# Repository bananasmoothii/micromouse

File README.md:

# [Bananasmoothii's Micromouse](https://github.com/bananasmoothii/micromouse)

A school project aiming to make a Micromouse robot and make it solve a maze (with official-size cells: 18x18 cm).

## Flash and run code

Install [Rust](https://doc.rust-lang.org/cargo/getting-started/installation.html) and [probe-rs](https://probe.rs/)
with one of the methods in their docs. Then plug the STM32F446RE Nucleo board via USB and flash and run with:

```sh
cargo run
```

(configured in `./.cargo`)

The robot has a power mechanism that cuts power when battery isn't charged enough, but this requires you to
maintain the button (on the back custom PCB) pressed when flashing the MCU. I recommend having an IDE keyboard
shortcut for this command. Flashing often fails on the first try, if it does just try again.

## Hardware used

* Nucleo board (with ST-Link): MCU is STM32F446RE
* Monster Moto shield
*
Two [IGARASHI N 2738-45 motors](https://www.conrad.fr/fr/p/moteur-universel-a-balais-brushed-igarashi-2738-048-gfc-3-244503.html)
*
One [LiPo 2S battery](https://www.conrad.fr/fr/p/reely-pack-de-batterie-lipo-7-4-v-350-mah-nombre-de-cellules-2-25-c-softcase-bec-2617149.html)
(6V - 8.4V) (bought two for using one while the other charges)
* Two 3144 Hall sensors (magnet → `DOUT = HIGH`) for odometry (12 magnets per wheel)
* One MPU 9250 (accelerometer + gyroscope + magnetometer + temperature sensor)
* Three VL53L1X distance sensors
* Tires are made from [20x7mm elastics](https://www.amazon.fr/dp/B0D9K3PJJF)
* [Cylindrical magnets, 2mm wide](https://www.amazon.fr/dp/B08NDRXGQX)

## [CAD models](https://cad.onshape.com/documents/aaf7a6983651c7702bceaa13/w/41b76918edb6f00955c96fe0/e/62dd90809362918a445464ef?renderMode=0&uiState=6a1494e0c7839ab38c881d4a)

This repo contains almost everything related to this project except the CAD models in the Onshape link above.

* The chassis is laser-cut from 3mm-thick wood and assembled with wood glue for the most stressed parts
* The wheels are made of laser-cut acrylic (wood not being resistant enough for gearing) pieces superglued together

  Note: In Onshape, the wheels are solid, you need the **Kiri:Moto** plugin to slice in 5mm slices and export as SVG for
  the laser cutter.
* The shafts are shoulder screws (unthreaded shoulder acting as the axle) screwed directly into the wooden chassis
* The smallest gear that's directly on the motors' shaft are metal, bought them
  [here](https://www.conrad.fr/fr/p/acier-roue-a-denture-frontale-reely-type-de-module-0-5-o-de-percage-2-3-mm-nombre-de-dents-12-240354.html)
* Kerf compensation was set to **0.16mm** for me (set in Kiri:Moto)

## Build & assembly manual

A full step-by-step guide to cutting the chassis, assembling the mechanics, and mounting all
electronics is available in
[issues_and_knowledge/build_manual.md](issues_and_knowledge/build_manual.md).

## Issues encountered and solutions found

A summary of the main problems hit during development — I²C crashes, missed encoder ticks,
Embassy async pitfalls, the trajectory-point-list dead end, and more — along with the solutions,
is documented in
[issues_and_knowledge/issues_list.md](issues_and_knowledge/issues_list.md).

### Robot overview

## Custom PCB

Files for the custom pcb are in the `pcb` folder and can be opened with [KiCad](https://www.kicad.org/).

### Export for manufacturing with JLCPCB

I used JLCPCB to manufacture and assemble the PCB. For generating the production files, install this KiCad plugin:

> **Fabrication Toolkit**
>
> Toolkit for automating PCB fabrication process with KiCad and JLC PCB.
>
> Features:
> - Generates gerber files in correct format for production.
> - Generates BOM file in correct format for production.
> - Generates Pick and Place file in correct format for assembly.
> - Automatic and manual component translations.
> - Many more unique additional features.

Production files will be generated in `pcb/production`. The files you're gonna need for JLCPCB are:

- `pcb.zip` (contains the Gerber files)

And for PCB assembly (PCBA):

- `bom.csv` (Bill Of Materials)
- `positions.csv` as "CPL" (Component Placement List)

## How to debug

Debugging on microcontroller can be quite tricky. For example, on the STM32F446RE, you can have **up to 6 breakpoints**
enabled, and debugging works through probe-rs. If the probe-rs' GDB stub doesn't work (probably because
[this issue](https://github.com/probe-rs/probe-rs/issues/3805) hasn't been fixed yet), try debugging through DAP.

### On VSCode

Probe-rs has made it easy to debug with VSCode thanks to an extension as explained
[here](https://probe.rs/docs/tools/debugger/)

### On RustRover

There is also an extension that can debug through DAP but it is less straight-forward:

1. Install the "lsp4ij" extension.
2. Set it up
   using [this tutorial](https://github.com/redhat-developer/lsp4ij/blob/main/docs/dap/user-defined-dap/codelldb.md).
    * At the end, you should use "attach" instead of "launch" with these parameters:

```json
{
  "chip": "STM32F446RE",
  "coreConfigs": [
    {
      "programBinary": "${file}"
    }
  ]
}
```

Note: RTT does not work here (I tried with `rttEnabled`).

## Repository structure

**For more information, see [architecture.md](issues_and_knowledge/architecture.md)**

```
micromouse/
├── src/
│   ├── main.rs                   — Embassy entry point: heap init, peripheral setup, task spawning
│   ├── dimensions.rs             — Physical constants (cell size, wall thickness, wheel geometry)
│   ├── i2c_devices.rs            — Sequential XSHUT-based I2C init for the 3 ToF sensors
│   ├── flash_log.rs              — For storing logs in flash memory
│   ├── labyrinth.rs              — 16×16 maze grid, probabilistic wall detection, pathfinding (flood-fill)
│   ├── utils.rs                  — Shared utilities
│   ├── panic_handler.rs          — Custom panic handler (logs then halts)
│   │
│   ├── devices/                  — Hardware drivers
│   │   ├── motors.rs             — DC motor PI feedback loop, reads waypoints from PATH_CHANNEL
│   │   ├── hall_sensor_3144.rs   — Interrupt-driven wheel encoders (AtomicI32 tick counters)
│   │   ├── mpu9250.rs            — 9-DOF IMU over SPI (accel, gyro, magnetometer)
│   │   ├── battery.rs            — 2-cell LiPo voltage monitoring via ADC
│   │   ├── buzzer.rs             — PWM audio (TIM2), command channel-driven
│   │   └── vl53lxx/              — ToF distance sensors
│   │       ├── vl53l0x.rs        — VL53L0X driver (unused, kept for reference)
│   │       └── vl53l1x.rs        — VL53L1X driver (distance sensors, runtime I2C address change)
│   │
│   ├── positioning/              — Sensor fusion and position tracking
│   │   ├── mod.rs                — positioning_task: 20 ms sensor-fusion loop
│   │   ├── odometry.rs           — Skid-steering wheel kinematics
│   │   ├── mpu.rs                — Gyro → yaw, magnetometer → absolute heading
│   │   ├── fusion.rs             — Kalman Filter (odometry + gyro + magnetometer)
│   │   └── types.rs              — Position2D, MovementDelta
│   │
│   └── trajectory/               — Path planning and motion profiling
│       ├── mod.rs                — Converts cell path → smooth velocity-profiled segments
│       ├── straight_line.rs      — Straight segment with trapezoidal velocity profile
│       └── in_place_turn.rs      — In-place rotation segment
│
├── docs/                         — Hosted on https://bananasmoothii.github.io/micromouse/
│   └── timeline/                 — Project timeline web app (photos, videos, notes)
│
├── pcb/                          — KiCad files for the custom PCB
│   └── production/               — JLCPCB production and assembly files
│
├── issues_and_knowledge/         — Notes on hardware quirks, bugs, and build documentation
│   ├── architecture.md           — High-level architecture overview
│   ├── build_manual.md           — Step-by-step build & assembly manual (translated from Rapport.docx)
│   ├── build_manual/             — Images referenced by build_manual.md
│   ├── issues_list.md            — Issues encountered and solutions found (translated from Rapport.docx)
│   ├── embassy_exti_missed_ticks_fix.md
│   ├── i2c_registers_and_pullups_explained.md
│   ├── monster moto shield ressources.md
│   └── vl53l1x_i2c_bsy_lockup_recovery.md
│
├── tools/                        — Various python scripts for analyzing logs with graphs or other things
│   └── clean_svg.py              — Replaces polyline-approximated circles in Kiri:Moto SVG exports with true SVG circles (fixes laser cutter charring)
│
├── build.rs                      — Build script (linker script selection)
├── Cargo.toml                    — Dependencies and patch section for forked sensor crates
├── memory.x                      — Linker memory map for STM32F446RE
└── .cargo/config.toml            — Default target (thumbv7em-none-eabi), runner (probe-rs), log level
```

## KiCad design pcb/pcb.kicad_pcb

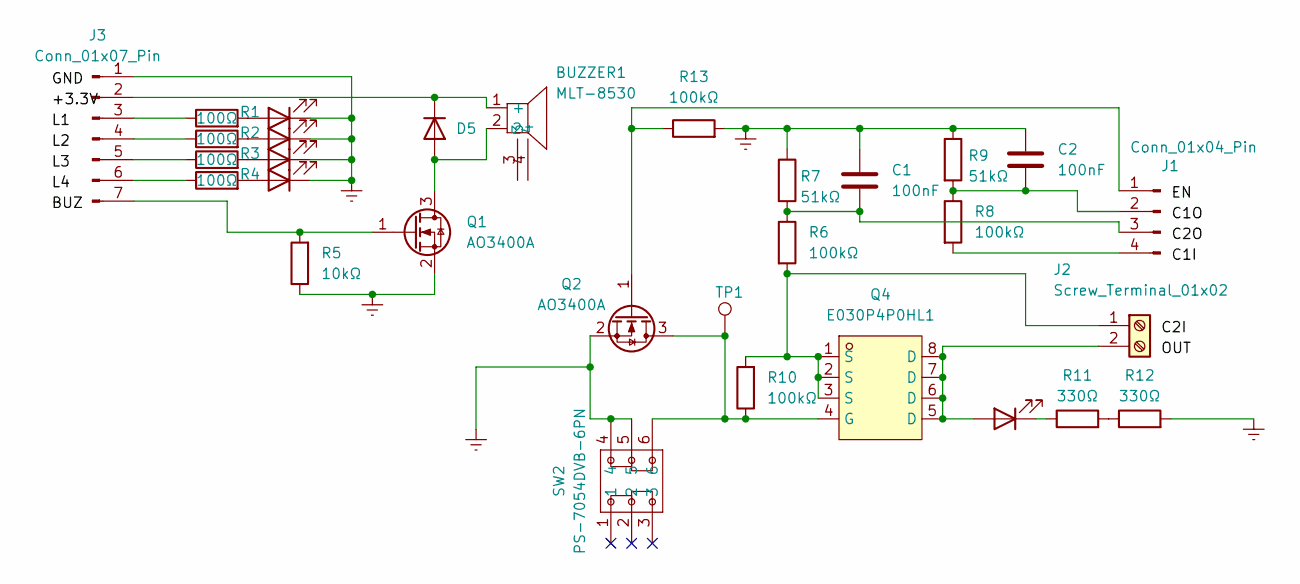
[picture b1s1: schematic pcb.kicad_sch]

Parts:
BUZZER1: MLT-8530; BUZ-SMD_4P-L8.5-W8.5-P8.50-BR; MPN MLT-8530; LCSC Part C94599
C1, C2: 100nF; C_0402_1005Metric
D1, D2, D3, D4: KT-0805G; LED_0805_2012Metric
D5: 1N4148WS; D_SOD-323
D6: KT-0603R; LED_0603_1608Metric
J1: Conn_01x04_Pin; PinHeader_1x04_P2.54mm_Vertical
J2: Screw_Terminal_01x02; CONN-TH_2P-P5.08_JL500-50002G01
J3: Conn_01x07_Pin; PinHeader_1x07_P2.54mm_Vertical
Q1, Q2: AO3400A; SOT-23
Q4: E030P4P0HL1; DFN-8_L5.8-W4.9-P1.27-LS6.1-BL-2; MPN E030P4P0HL1; LCSC Part C29781150
R1, R2, R3, R4: 100Ω; R_0402_1005Metric
R5: 10kΩ; R_0402_1005Metric
R6, R8, R10, R13: 100kΩ; R_0402_1005Metric
R7, R9: 51kΩ; R_0402_1005Metric
R11, R12: 330Ω; R_0402_1005Metric
SW2: PS-7054DVB-6PN; SW-TH_6P-L7.0-W7.0-P2.00; MPN PS-7054DVB-6PN; LCSC Part C22363820
TP1: TestPoint; TestPoint_Pad_1.5x1.5mm

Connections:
Earth: C1.1, C2.1, D1.1 (K), D2.1 (K), D3.1 (K), D4.1 (K), J3.1, Q1.2 (S), Q2.2 (S), R5.1, R7.1, R9.1, R12.2, R13.2, SW2.4, SW2.5
unnamed: BUZZER1.1 (+), D5.1 (K), J3.2
unnamed: D1.2 (A), R1.2
unnamed: D2.2 (A), R2.2
unnamed: D3.2 (A), R3.2
unnamed: D4.2 (A), R4.2
unnamed: BUZZER1.2, D5.2 (A), Q1.3 (D)
unnamed: D6.2 (A), J2.2, Q4.5 (D), Q4.6 (D), Q4.7 (D), Q4.8 (D)
unnamed: D6.1 (K), R11.1
unnamed: J1.1, Q2.1 (G), R13.1
unnamed: C2.2, J1.2, R8.1, R9.2
unnamed: C1.2, J1.3, R6.1, R7.2
unnamed: J1.4, R8.2
unnamed: J2.1, Q4.1 (S), Q4.2 (S), Q4.3 (S), R6.2, R10.2
unnamed: J3.3, R1.1
unnamed: J3.4, R2.1
unnamed: J3.5, R3.1
unnamed: J3.6, R4.1
unnamed: J3.7, Q1.1 (G), R5.2
unnamed: Q2.3 (D), Q4.4 (G), R10.1, SW2.6, TP1.1 (1_1)
unnamed: R11.2, R12.1

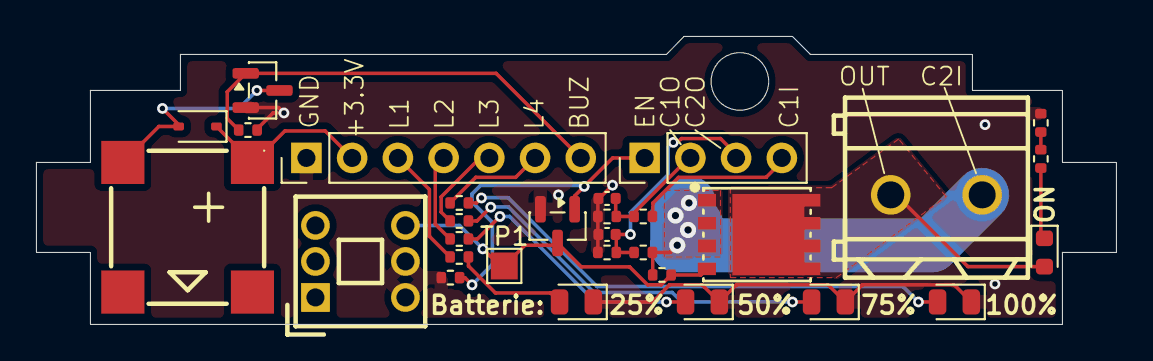
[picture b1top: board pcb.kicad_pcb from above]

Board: 2 copper layers, 60.0 x 16.0 mm, 30 parts (0 on the bottom side), 21 nets.

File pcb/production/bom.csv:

Designator,Footprint,Quantity,Value,LCSC Part #
BUZZER1,BUZ-SMD_4P-L8.5-W8.5-P8.50-BR,1,MLT-8530,C94599
"C1, C2",0402,2,100nF,
"D1, D2, D3, D4",0805,4,KT-0805G,
D5,D_SOD-323,1,1N4148WS,
D6,0603,1,KT-0603R,
J1,PinHeader_1x04_P2.54mm_Vertical,1,Conn_01x04_Pin,
J2,CONN-TH_2P-P5.08_JL500-50002G01,1,Screw_Terminal_01x02,C709041
J3,PinHeader_1x07_P2.54mm_Vertical,1,Conn_01x07_Pin,
"Q1, Q2",SOT-23,2,AO3400A,
Q4,DFN-8_L5.8-W4.9-P1.27-LS6.1-BL-2,1,E030P4P0HL1,C29781150
"R1, R2, R3, R4",0402,4,100Ω,
"R10, R13, R6, R8",0402,4,100kΩ,
"R11, R12",0402,2,330Ω,
R5,0402,1,10kΩ,
"R7, R9",0402,2,51kΩ,
SW2,SW-TH_6P-L7.0-W7.0-P2.00,1,PS-7054DVB-6PN,C22363820
TP1,TestPoint_Pad_1.5x1.5mm,1,TestPoint,

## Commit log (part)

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2026-01-29 srjstrh
    Took 1 hour 35 minutes
2026-01-29 gitignore
    Took 19 seconds
2026-01-29 DEBUG.md
    Took 29 minutes
2026-01-30 sfhn
    Took 3 hours 16 minutes
2026-02-01 dtn
    Took 2 hours 42 minutes
2026-02-01 IT FUCKING WORKS
    Took 51 minutes
2026-02-01 cleanup, use interrupts
    Took 2 hours 1 minute
2026-02-01 refactor, better prints
    Took 32 minutes
2026-02-01 make it more robust
    Took 1 hour 8 minutes
2026-02-01 re-add button
    Took 3 minutes
2026-02-02 small things
    Took 11 minutes
2026-02-02 refactor
    Took 1 hour 43 minutes
2026-02-02 end refactor
    Took 1 hour 10 minutes
2026-02-02 end refactor
    Took 17 seconds
2026-02-02 cleanup
    Took 7 minutes
2026-02-02 more cleanup
    Took 1 minute
2026-02-02 more cleanup x2
    Took 4 minutes
2026-02-02 tried to use vl53l0x
    Took 1 hour 19 minutes
2026-02-02 forgot to spawn task
    Took 16 minutes
2026-02-02 fix interrupt deadlock
    Took 5 minutes
2026-02-09 temp
    Took 55 minutes
2026-02-09 update dependencies to use my fork
    Took 28 minutes
2026-02-09 ?
    Took 28 seconds
2026-02-12 try using async vl53l0x
    Took 5 hours 23 minutes
2026-02-12 fix everything back
    Took 1 hour 10 minutes
2026-02-12 lots of fixes
    Took 1 hour 1 minute
2026-02-12 cleanup
    Took 2 minutes
2026-02-13 update cargo, *
    Took 10 minutes
2026-02-15 two sensors
    Took 1 hour 0 minutes
2026-02-15 don't report phase fails
    Took 21 minutes
2026-02-17 refactor
    Took 5 hours 36 minutes
2026-03-04 mpu works, simplified vl53l1x driver wrapper
    Took 4 hours 33 minutes
2026-03-04 f
    Took 19 seconds
2026-03-11 debugging
    Took 13 hours 57 minutes
2026-03-11 nothing works anymore yay
    Took 47 minutes
2026-03-11 Revert "nothing works anymore yay"
    This reverts commit 37cf85aa56bebcb38e7d65a42ca8bad8044233e8.
    Took 20 minutes
2026-03-11 cleanup
    Took 28 minutes
2026-03-12 refactor, start working on motors (after 63h of project yay)
    Took 4 hours 8 minutes
2026-03-12 refactor, display cell voltages
    Took 1 hour 59 minutes
2026-03-13 motor works
    Took 2 hours 45 minutes
2026-04-17 add hall sensor continuous measuring functionality
    Took 27 minutes
2026-04-17 PCB !! (open with KiCad) / produce with pcb.zip, bom.csv & positions.csv
    Took 3 minutes
2026-04-17 ?
    Took 26 seconds
2026-04-17 Vibe-coded odometry and mpu positioning
    Took 49 minutes
2026-04-17 Refactor positioning with channel-based tasks and Kalman filters - Migrate to a channel-based positioning task architecture - Implement 1D Kalman filter for orientation (including compass) - Implemen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
    Took 1 hour 15 minutes
2026-04-18 format
    Took 16 seconds
2026-04-18 refactoring & documentation
    Took 51 minutes
2026-04-18 refactoring & corrections
    Took 59 minutes
2026-04-21 vibe-code Refactor odometry and motor control using atomic variables for tick tracking
    Took 1 hour 39 minutes
2026-04-22 added labyrinth.rs
2026-04-22 started trajectory
2026-04-22 fix no lab
2026-04-23 add dual-motor overcurrent protection and fault handling formatting
    Took 13 seconds
2026-04-23 refactor to right folder
    Took 13 minutes
2026-04-23 vibe code trajectory
    Took 8 minutes
2026-04-23 research.md
    Took 12 minutes
2026-04-23 trajectory optimisation
    Took 2 hours 11 minutes
2026-04-23 revert wrongly reported unused
    Took 56 seconds
2026-04-25 buzzer works
    Took 1 hour 5 minutes
2026-04-25 buzzer tweaked
    Took 12 minutes
2026-04-26 work on vl53l1x sensors
    Took 4 hours 30 minutes
2026-04-26 tried to make an I2C recovery system
    Took 1 hour 33 minutes
2026-04-26 FIXED I2C RECOVERY I LOVE CLAUDE
    Took 46 minutes
2026-04-26 use n.hz()
    Took 3 minutes
2026-04-26 ALL SENSORS WORK
    Took 21 minutes
2026-04-26 tweak buzzer
    Took 10 minutes
2026-04-28 Fix merge, add things
    Took 2 hours 13 minutes
2026-04-28 fix distance sensors again (apparently some pins don't work)
    Took 43 minutes
2026-04-28 AI things
    Took 37 minutes
2026-04-28 fix odometry
    Took 1 hour 51 minutes
2026-04-28 fix velocity calculations
    Took 18 minutes
2026-04-28 fix velocity calculations better
    Took 53 minutes
2026-04-28 smoother trajectory
    Took 27 minutes
2026-05-07 wipe everything
    Took 48 minutes
2026-05-07 Refactoring & cleaning of hall sensor + MPU, add docs for Kalman filter constants
    Took 1 hour 37 minutes
2026-05-08 Straight line seems done
    Took 2 hours 59 minutes
2026-05-08 logs and things, need wheels to continue
    Took 35 minutes
2026-05-13 debug
    Took 16 minutes
2026-05-13 simplify, make speed to PWM depend on battery voltage
    Took 2 hours 23 minutes
2026-05-13 tweak start
    Took 22 minutes
2026-05-13 add flash_log.rs, use one flash sector for log
    Took 24 minutes
2026-05-14 Fix hall sensor tick count at medium - high speed, continue trying to find the correct PI constants along with PWM_TO_SPEED_FACTOR
    Took 3 hours 51 minutes
2026-05-14 Code cleanup, change velocity calculation to dx/dt instead of counting tick
    Took 44 minutes
2026-05-15 Documentation about the true identity of what the hell we are doing here
    Took 34 minutes
2026-05-15 Pivot turn: dyn TrajectorySegment, velocity-dependent motor cutoff
    - Add async-trait to make TrajectorySegment dyn-compatible; motor_tests
    now uses Vec<Box<dyn TrajectorySegment>> for sequential execution
    - Replace fixed DONE_THRESHOLD_RAD with physics-based cutoff:
    cut when remaining <= omega^2 / (2 * FRICTION_DECEL), where
    FRICTION_DECEL=490 rad/s^2 derived from observed 22° coast at ~19.6 rad/s
    - Add APPROACH_SPEED=0.5 m/s for the final 30°, separate from MIN_TURN_SPEED
2026-05-16 OVERSHOOOT
    Took 3 hours 41 minutes
2026-05-16 tweak
    Took 1 hour 12 minutes
2026-05-16 reenable distance sensors
    Took 8 minutes
2026-05-16 reenable distance sensors
    Took 46 seconds
2026-05-16 fix release mode with opt-level=1 on embassy-stm32 crate
    Took 1 hour 27 minutes
2026-05-17 Cleanup
    Took 20 minutes
2026-05-18 Things
    Took 1 hour 19 minutes
2026-05-18 Meh-working DistanceToFrontWall
2026-05-18 Removed all unnecessary code for minimal example of embassy-stm32 optimization issue
    Took 21 minutes
2026-05-18 removed more files
    Took 3 minutes
2026-05-18 removed interrupts
    Took 4 minutes
2026-05-18 restart wall folowing from scratch
    Took 33 minutes
2026-05-18 rewrite start
    Took 45 minutes
2026-05-18 Fix wall steering
    Took 2 hours 29 minutes
2026-05-19 Improve wall steering
    Took 55 minutes
2026-05-19 WALL FOLLOWING WORKS
    Took 31 minutes
2026-05-20 Fix I2C sensor polling with round-robin
    Took 2 hours 17 minutes
2026-05-20 yeah wall following still
    Took 1 hour 4 minutes
2026-05-20 Almost perfect straight line in corridor !
    Took 3 hours 45 minutes
2026-05-20 Alright, can't do more without Fablab
    Took 34 minutes
2026-05-20 Timeline website !
    Took 2 minutes
2026-05-20 new data
2026-05-20 new data 2
    Took 38 seconds
2026-05-20 start Presentation Soutenance.pptx
    Took 2 minutes
2026-05-20 try one for DistanceToFrontWall(x)
    Took 51 minutes
2026-05-21 README.md
    Took 1 hour 20 minutes
2026-05-21 forgot this
    Took 3 minutes
2026-05-21 move timeline to /docs for github
2026-05-21 update README.md
    Took 6 minutes
2026-05-21 try update
    Took 3 minutes
2026-05-21 fix data.js
    Took 1 minute
2026-05-21 add feature
    Took 7 minutes
2026-05-21 straight line with DistanceToFrontWall works when start position is perfect
    Took 1 hour 17 minutes
2026-05-21 fix a little bit straightline when starting not perfectly aligned
    Took 15 seconds
2026-05-21 WORKS
    Took 6 minutes
2026-05-21 IT FUCKING WORKS
    Took 6 minutes
2026-05-21 labyrinth -> LabyrinthPlan -> TrajectorySegment
    Took 39 minutes
2026-05-21 I'm done with this (still doesn't really work)
    Took 1 minute
2026-05-23 soutenance de merde
    Took 1 hour 31 minutes
2026-05-25 Add docs & small cleanup
    Took 29 minutes
2026-05-25 Add folder structure in README.md
    Took 9 minutes
2026-05-26 add build_manual.md
    Took 1 hour 17 minutes
2026-05-27 LICENSE
    Took 24 minutes
2026-05-28 more docs
    Took 41 minutes
2026-05-28 done ?
    Took 3 hours 41 minutes
2026-05-29 done I think
    Took 38 minutes
2026-06-02 Use local embassy path for testing latest version and update code
    Took 35 seconds
